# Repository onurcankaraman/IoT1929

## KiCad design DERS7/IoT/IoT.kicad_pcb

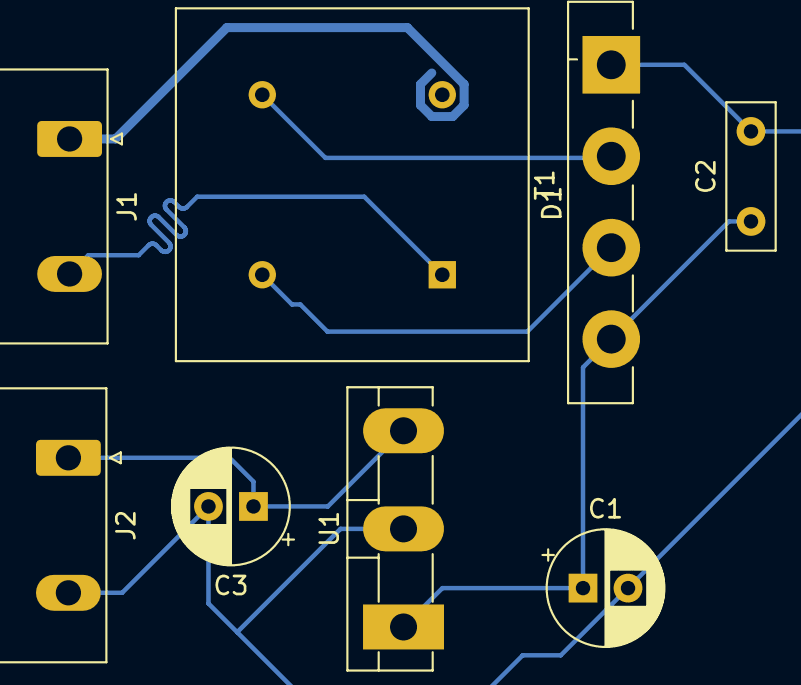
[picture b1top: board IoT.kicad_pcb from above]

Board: 2 copper layers, 8 parts (0 on the bottom side), 6 nets.

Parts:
C1: 220uF; CP_Radial_D6.3mm_P2.50mm
C2: 10nF; C_Disc_D8.0mm_W2.5mm_P5.00mm
C3: 2200uF; CP_Radial_D6.3mm_P2.50mm
D1: D_Bridge_-AA+; Diode_Bridge_Vishay_GBU
J1, J2: Conn_01x02; PhoenixContact_GMSTBA_2,5_2-G_1x02_P7.50mm_Horizontal
T1: 220; Transformer_NF_ETAL_P1165
U1: L7815; TO-3P-3_Vertical

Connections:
GND: C1.2, C2.2, C3.2, D1.1, J2.2, U1.2
unnamed: C1.1, C2.1, D1.4, U1.1
unnamed: C3.1, J2.1, U1.3
unnamed: D1.2, T1.4
unnamed: D1.3, T1.3
unnamed: J1.2, T1.1

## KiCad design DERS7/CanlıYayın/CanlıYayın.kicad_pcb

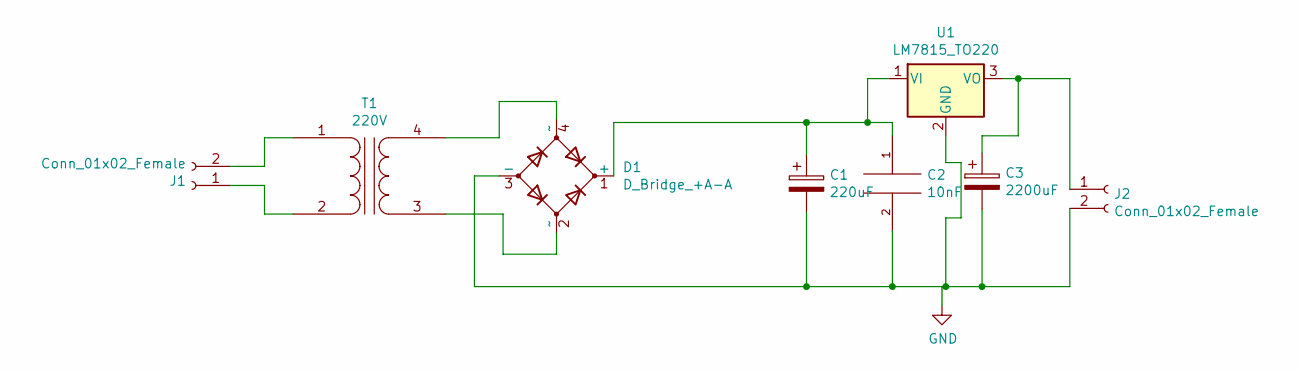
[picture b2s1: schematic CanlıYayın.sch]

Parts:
C1: 220uF; CP_Radial_D10.0mm_P2.50mm
C2: 10nF; CP_Radial_D10.0mm_P2.50mm
C3: 2200uF; CP_Radial_D10.0mm_P2.50mm
D1: D_Bridge_+A-A; Diode_Bridge_Vishay_KBU
J1: Conn_01x02_Female; PinHeader_1x02_P2.54mm_Horizontal
J2: Conn_01x02_Female; PinHeader_1x02_P2.54mm_Vertical
T1: 220V; Transformer_Toroid_Horizontal_D9.0mm_Amidon-T30
U1: LM7815_TO220; TO-220-3_Vertical

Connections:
GND: C1.2, C2.2, C3.2, D1.3 (-), J2.2, U1.2 (GND)
unnamed: C1.1, C2.1, D1.1 (+), U1.1 (VI)
unnamed: C3.1, J2.1, U1.3 (VO)
unnamed: D1.2 (~~), T1.3 (SA)
unnamed: D1.4 (~~), T1.4 (SB)
unnamed: J1.1, T1.2 (AB)
unnamed: J1.2, T1.1 (AA)

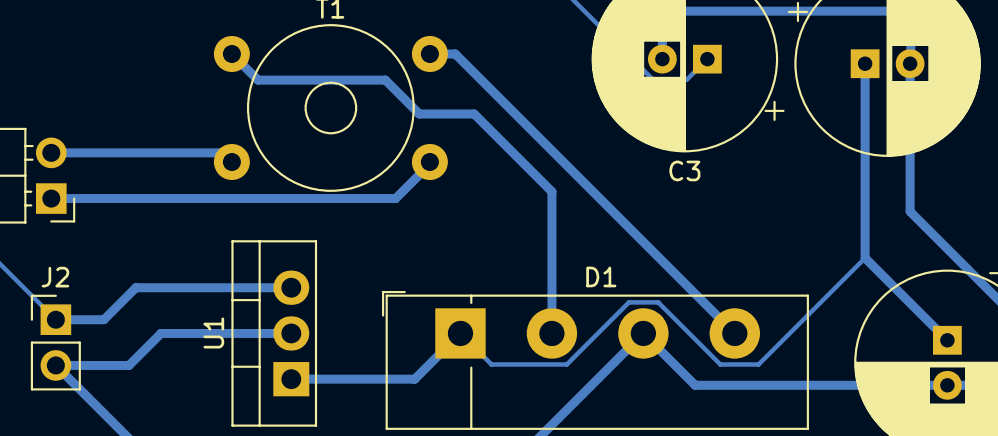
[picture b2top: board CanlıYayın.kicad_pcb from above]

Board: 2 copper layers, 8 parts (0 on the bottom side), 7 nets.

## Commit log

2021-02-27 İlk Ders Sunusu
2021-02-27 Ders Örnekleri
2021-02-28 2. Ders İçerikleri
2021-02-28 Kod Örnekleri
2021-03-06 3. Ders Güncellemeleri
2021-03-06 Ders3- Devre1
2021-03-07 Çalgan Hocanın Kodları
2021-03-07 Devre
2021-03-09 GamePad Devre
2021-03-13 Ders5
2021-03-13 ı2c Örneği
2021-04-04 Ders7
